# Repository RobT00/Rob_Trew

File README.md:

# Rob_Trew
Amalgamation of Assembly Code I have written  
Each branch in this Repo contains a language and associted projects/assignments

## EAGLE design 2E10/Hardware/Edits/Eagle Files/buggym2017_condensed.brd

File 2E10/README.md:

# Rob_Trew
Arduino Code for the Buggy as part of the 2E10 "Buggy Project"

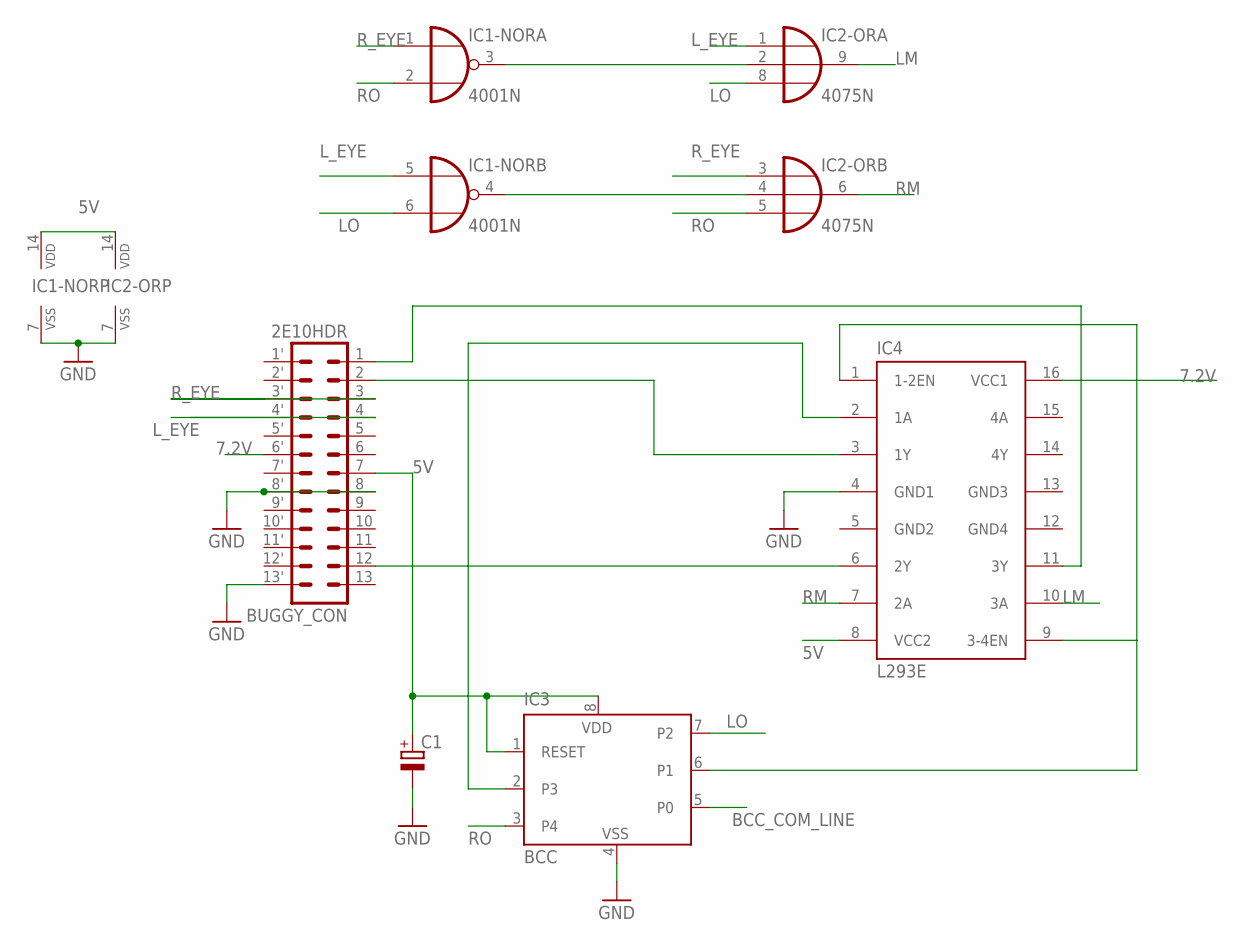
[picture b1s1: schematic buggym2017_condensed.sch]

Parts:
BUGGY_CON: 2E10HDR; 2E10BOARD
C1: CPOL-EUE5-4; E5-4
IC1-NOR: 4001N; DIL14
IC2-OR: 4075N; DIL14
IC3: BCC; DIL8
IC4: L293E; DIL16

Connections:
5V: BUGGY_CON.7, C1.+, IC1-NOR.14 (VDD), IC2-OR.14 (VDD), IC3.1 (RESET), IC3.8 (5V), IC4.8 (VCC2)
7.2V: BUGGY_CON.6', IC4.16 (VCC1)
BCC_COM_LINE: IC3.5 (P0)
GND: BUGGY_CON.8, BUGGY_CON.8', BUGGY_CON.13', C1.-, IC1-NOR.7 (VSS), IC2-OR.7 (VSS), IC3.4 (VSS), IC4.4 (GND1)
GND2: IC4.5 (GND2)
GND3: IC4.13 (GND3)
GND4: IC4.12 (GND4)
LINK_1: IC1-NOR.3 (O), IC2-OR.2 (I1)
LINK_2: IC1-NOR.4 (O), IC2-OR.4 (I1)
LM: IC2-OR.9 (O), IC4.10 (3A)
LO: IC1-NOR.6 (I1), IC2-OR.8 (I2), IC3.7 (P2)
L_EYE: BUGGY_CON.4, BUGGY_CON.4', IC1-NOR.5 (I0), IC2-OR.1 (I0)
unnamed: IC3.2 (P3), IC4.2 (1A)
unnamed: BUGGY_CON.1, IC4.11 (3Y)
unnamed: BUGGY_CON.2, IC4.3 (1Y)
unnamed: BUGGY_CON.12, IC4.6 (2Y)
unnamed: IC3.6 (P1), IC4.1 (1-2EN), IC4.9 (3-4EN)
RM: IC2-OR.6 (O), IC4.7 (2A)
RO: IC1-NOR.2 (I1), IC2-OR.5 (I2), IC3.3 (P4)
R_EYE: BUGGY_CON.3, BUGGY_CON.3', IC1-NOR.1 (I0), IC2-OR.3 (I0)

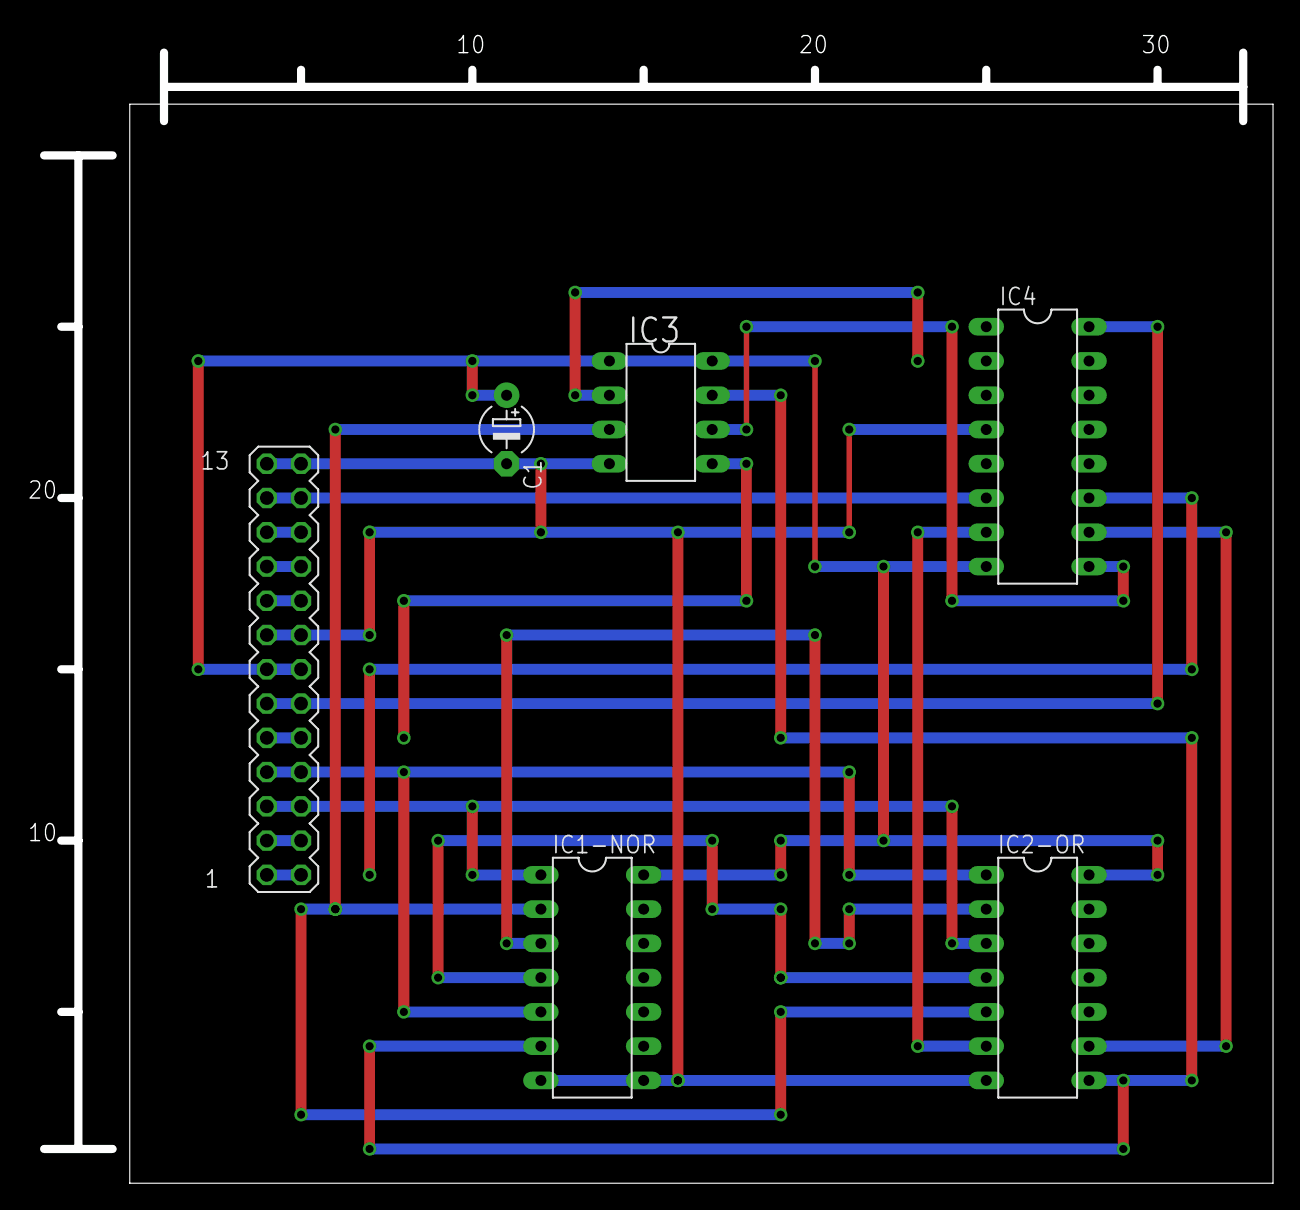
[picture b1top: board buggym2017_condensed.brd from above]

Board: 2 copper layers, 91.8 x 85.1 mm, 6 parts (0 on the bottom side), 16 nets.

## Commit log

2018-09-13 Added Python for Lab 1 in 4C16
2018-09-13 Adding Python content to python branch
2018-09-13 Removed 'Python' from master branch
2018-09-13 Created branch containg all C-based languages
2018-09-13 Updates made to Lab 1
2018-09-14 Added college work to date
2018-09-14 Code from 2E10 Buggy Project
2018-09-14 Issue with 2E10
2018-09-15 Finihsed ver 1 of Lab 1
2018-09-15 Updates to Lab 1
2018-09-15 Removed Python 3.6 element
2018-09-15 Added ARM Assembly Code
2018-09-15 Added 3D1 readme
2018-09-15 Added README
2018-09-15 Added README for 4C16
2018-09-15 Added README for Lab 1
2018-09-15 Added Buggy code from 2E10 Project
2018-09-15 Added Testing code from 3C8 Projects
2018-09-16 Added 2E11 content
2018-09-16 Added 3C7 Files
2018-09-17 Updates to Lab 1, added arguments to loops
2018-09-17 Possible finish of Lab 1
2018-09-17 Small edits
2018-09-17 Running in Python 3.6.6
2018-09-18 Changes to Lab 1 for optimal fit finding
2018-09-18 Still looking for nice way to find optimal order fit
2018-09-19 Added Lab 0
2018-09-19 Added Lab 2
2018-09-19 Added Lab 3
2018-09-19 Added Lab 4
2018-09-19 Added Lab 5
2018-09-19 Added Lab 6
2018-09-19 Added Lab 7
2018-09-19 Added Jupyter Notebook
2018-09-19 Added Tutorial 1
2018-09-20 Started Tutorial 1
2018-09-20 Updated Assebly Code Langauge README files
2018-09-21 Finished Version 1 of Tutorial 1
2018-09-24 Added gitignore
2018-09-24 Updated gitignore
2018-09-24 Removed files not needed
2018-09-24 Started Lab 2
2018-09-24 Small changes for optimisation
2018-09-24 Progress made in Lab 2
2018-09-25 Finished Lab 2
2018-09-25 Updated Notebook
2018-09-25 Added caching files
2018-09-25 Accounted for negative numbers in gcd
2018-09-26 Updated Notebooks
2018-09-26 Started Tutorial 2, x64
2018-09-26 Updated .gitignore
2018-09-26 Set up for Tutorial 2
2018-09-26 Updated READMEs and File Structure
2018-09-26 Finished Tutorial 1
2018-09-26 Cleaned up Files
2018-09-26 Removed x64 folder
2018-09-29 Framework for Tutorial 2
2018-10-01 Code written for Tutorial 2
2018-10-01 Finished Tutorial 2
2018-10-02 Copied Jupyter Notebook for ease of use
2018-10-09 new file: cifar10-dataset.tar.gz
2018-10-09 Updates to Lab 4
2018-10-09 Now can use Lab 4
2018-10-10 Added .gitignore
2018-10-10 New changes to .gitignore
2018-10-10 Started Tutorial 3
2018-10-10 Starting Q1
2018-10-11 Files for MasterCard interview
2018-10-11 Lab 4, potentially complete
2018-10-13 Update gitignore
2018-10-13 changes to gitignore
2018-10-13 Ignores implemented
2018-10-13 Updates to generalise .gitignore
2018-10-13 Updates to Tutorial 3
2018-10-13 Nearly finished Tutorial 3
2018-10-13 Tutorial 3 largely complete
2018-10-13 Metrics for ackermann
2018-10-13 Finishing Tutorial 3
2018-10-14 Finished Tutorial 3
2018-10-15 Misc files
2018-10-17 Started Lab 5
2018-10-23 Added gitignore for Lab 6
2018-10-23 Started Lab 6
2018-10-24 Updates to Lab 6
2018-10-24 Rerun Lab 6
2018-10-24 Progress on Lab 6
2018-10-26 Lab 6 complete
2018-11-04 Notebook updates
2018-11-13 Updates to Lab 7
2018-11-15 Lab 6 clean-up
2018-11-15 Working on Lab 7, unreliable accuracies
2018-11-18 Cache in Tutorial 6
2018-11-18 Cleaned up Cache
2018-11-18 Added READMEs
2018-11-18 Started Matrix Multiplication
2018-11-18 Modified for Transpose Multiplication
2018-11-18 Finished Tutorial 6
2018-11-19 Lab 7 updates
2018-11-21 Model Progress
2018-11-21 Progress?
2018-11-30 Progress in lab
2018-12-01 End of Cluster Time
2019-09-16 Updates to Deep Dream scripts and .gitignore
2019-09-16 Added CS7CS4, with Data
2019-09-17 Initial commit for task work
2019-09-26 Updated Lab 7 script with local edits
2019-09-30 Removed tmp folders from tracked files
2019-09-30 Progress on CS7CS4 lab
2019-10-03 Moved CS7CS4 work to private GitLab Repo
